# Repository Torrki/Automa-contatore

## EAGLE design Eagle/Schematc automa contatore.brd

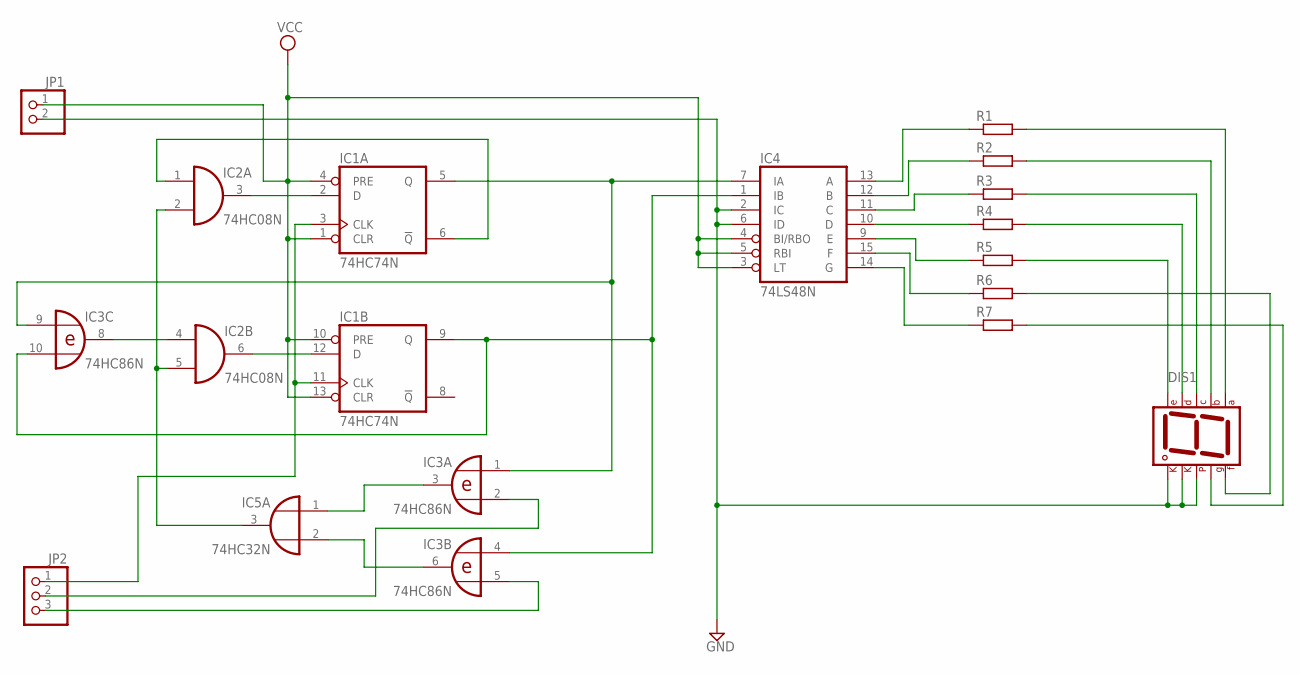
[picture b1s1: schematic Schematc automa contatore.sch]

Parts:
DIS1: 7SEG-CK; 7SEG-13
IC1: 74HC74N; DIL14
IC2: 74HC08N; DIL14
IC3: 74HC86N; DIL14
IC4: 74LS48N; DIL16
IC5: 74HC32N; DIL14
JP1: PINHD-1X2; 1X02
JP2: PINHD-1X3; 1X03
R1, R2, R3, R4, R5, R6, R7: R-EU_0204/5; 0204/5

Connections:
GND: DIS1.3 (CK1), DIS1.5 (DP), DIS1.8 (CK2), IC1.7 (GND), IC2.7 (GND), IC3.7 (GND), IC4.2 (IC), IC4.6 (ID), IC4.8 (GND), IC5.7 (GND), JP1.2
unnamed: IC1.5 (Q), IC3.1 (I0), IC3.9 (I0), IC4.7 (IA)
unnamed: IC1.9 (Q), IC3.4 (I0), IC3.10 (I1), IC4.1 (IB)
unnamed: IC1.2 (D), IC2.3 (O)
unnamed: IC1.12 (D), IC2.6 (O)
unnamed: IC1.6 (!Q), IC2.1 (I0)
unnamed: IC2.4 (I0), IC3.8 (O)
unnamed: IC3.3 (O), IC5.1 (I0)
unnamed: IC3.6 (O), IC5.2 (I1)
unnamed: IC2.2 (I1), IC2.5 (I1), IC5.3 (O)
unnamed: IC1.3 (CLK), IC1.11 (CLK), JP2.1
unnamed: IC3.2 (I1), JP2.2
unnamed: IC3.5 (I1), JP2.3
unnamed: IC4.13 (A), R1.1
unnamed: IC4.12 (B), R2.1
unnamed: IC4.11 (C), R3.1
unnamed: IC4.10 (D), R4.1
unnamed: IC4.9 (E), R5.1
unnamed: IC4.15 (F), R6.1
unnamed: IC4.14 (G), R7.1
unnamed: DIS1.7 (A), R1.2
unnamed: DIS1.6 (B), R2.2
unnamed: DIS1.4 (C), R3.2
unnamed: DIS1.2 (D), R4.2
unnamed: DIS1.1 (E), R5.2
unnamed: DIS1.9 (F), R6.2
unnamed: DIS1.10 (G), R7.2
VCC: IC1.1 (CLR), IC1.4 (PRE), IC1.10 (PRE), IC1.13 (CLR), IC1.14 (VCC), IC2.14 (VCC), IC3.14 (VCC), IC4.3 (LT), IC4.4 (BI/RBO), IC4.5 (RBI), IC4.16 (VCC), IC5.14 (VCC), JP1.1

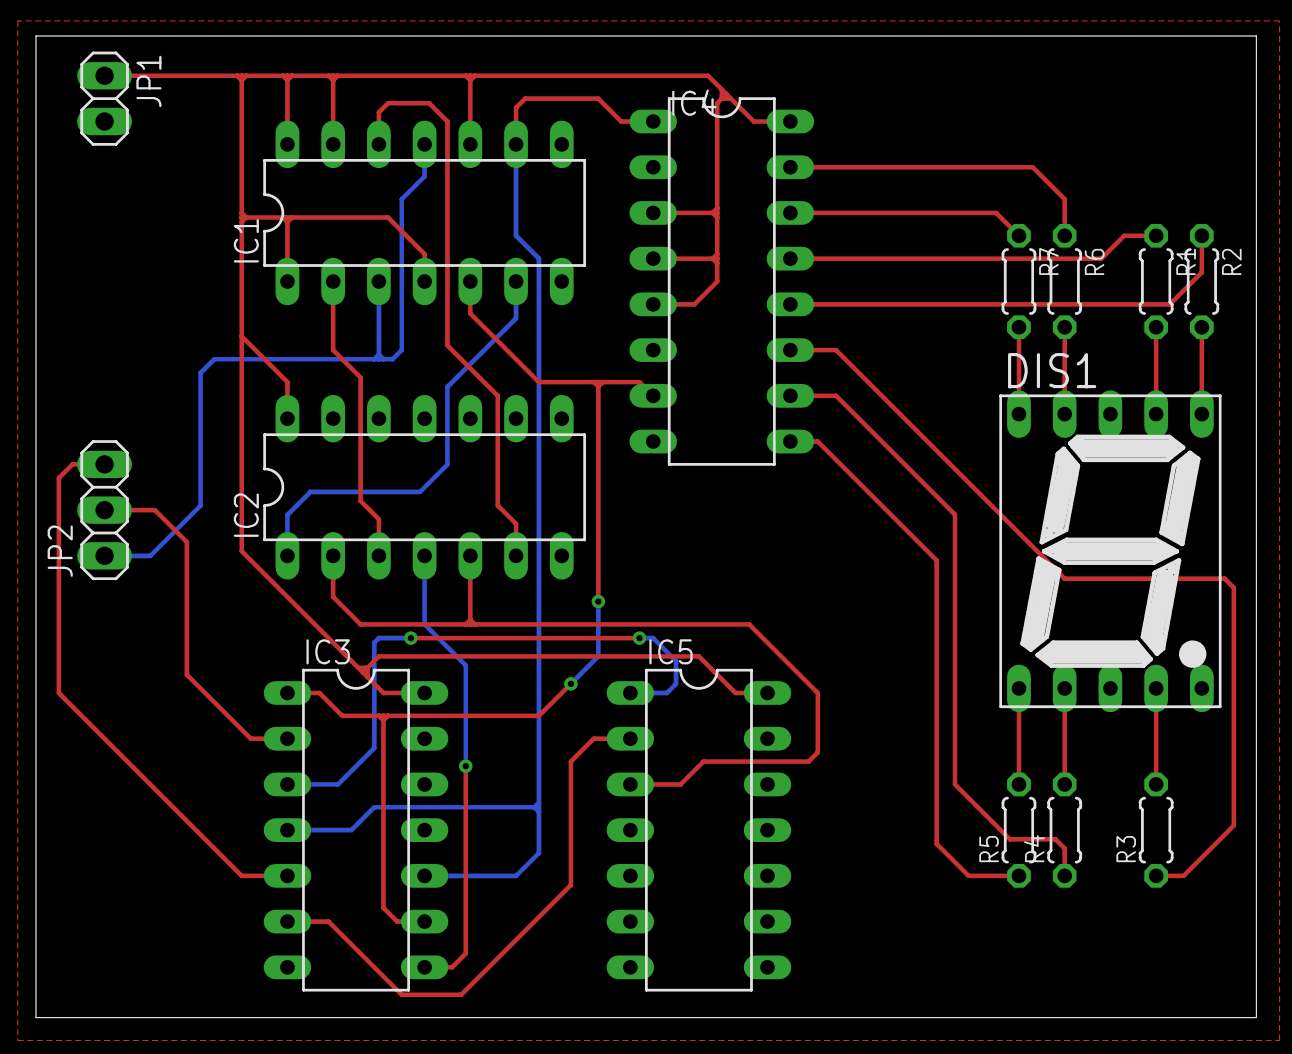
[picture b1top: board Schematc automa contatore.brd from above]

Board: 2 copper layers, 67.8 x 54.5 mm, 15 parts (0 on the bottom side), 28 nets.

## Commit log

2024-03-30 Init repository
